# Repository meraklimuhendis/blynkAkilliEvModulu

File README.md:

# blynkAkilliEvModulu

Bu projede ESP8266-07 ile uzaktan akıllı ev kontrolü yaptım. Ayrıntılı olarak video halinde izlemek isterseniz aşağıdaki videoya gidebilirsiniz.

Video ► https://youtu.be/qkML5l_z_RQ

/*

MERAKLI MÜHENDİS YOUTUBE KANALI

Youtube Kanalı için - https://bit.ly/2AEP5bf

Facebook Sayfası için - https://bit.ly/3qVqAMC

Discord Kanalımıza GEL! - https://bit.ly/347FlSp

Tüm sorularınızı discord kanalımızdan sorabilirsiniz. Orası teknik servis gibi :)

*/

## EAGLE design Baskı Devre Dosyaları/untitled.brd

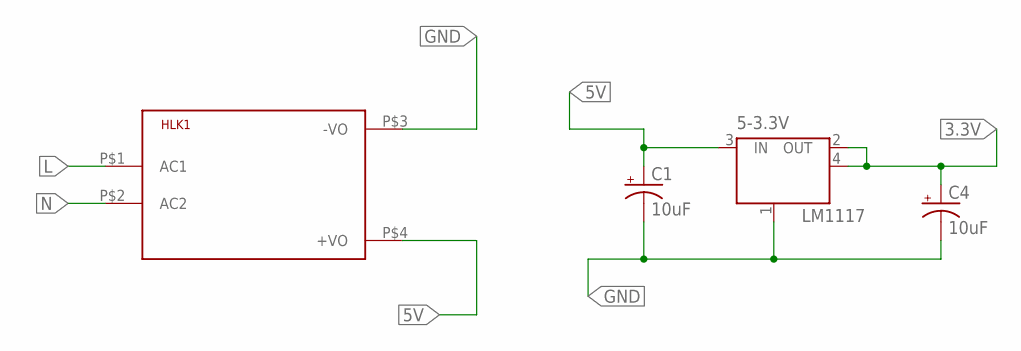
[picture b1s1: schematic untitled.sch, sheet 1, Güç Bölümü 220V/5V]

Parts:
5-3.3V: LM1117; SOT223
C1, C4: 10uF; EIA3216
HLK1: HLK-PM013W; HLK-PM01

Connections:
3.3V: 5-3.3V.2 (OUT), 5-3.3V.4 (OUT), C4.A (+); also elsewhere on the board
5V: 5-3.3V.3 (IN), C1.A (+), HLK1.P$4 (+VO); also elsewhere on the board
GND: 5-3.3V.1 (GND/ADJ), C1.C (-), C4.C (-), HLK1.P$3 (-VO); also elsewhere on the board
L: HLK1.P$1 (AC1); also elsewhere on the board
N: HLK1.P$2 (AC2); also elsewhere on the board

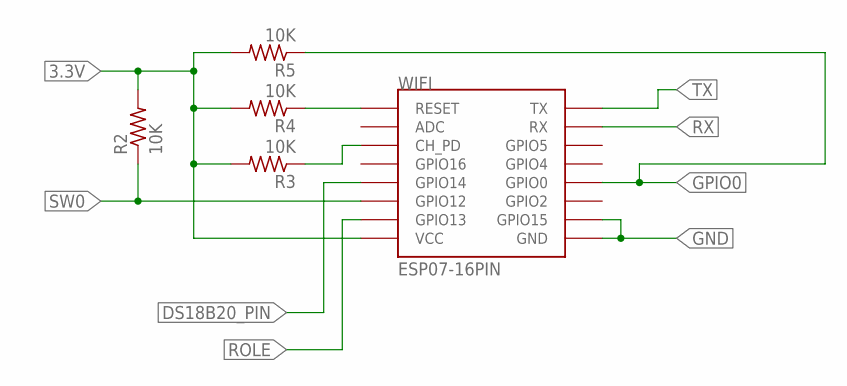
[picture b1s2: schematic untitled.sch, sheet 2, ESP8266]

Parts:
R2, R3, R4, R5: 10K; R0805
WIFI: ESP07-16PIN

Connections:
3.3V: R2.2, R3.2, R4.2, R5.2, WIFI.VCC; also elsewhere on the board
DS18B20_PIN: WIFI.GPIO14; also elsewhere on the board
GND: WIFI.GND, WIFI.GPIO15; also elsewhere on the board
GPIO0: R5.1, WIFI.GPIO0; also elsewhere on the board
unnamed: R4.1, WIFI.REST (RESET)
unnamed: R3.1, WIFI.CH_PD
ROLE: WIFI.GPIO13; also elsewhere on the board
RX: WIFI.RX; also elsewhere on the board
SW0: R2.1, WIFI.GPIO12; also elsewhere on the board
TX: WIFI.TX; also elsewhere on the board

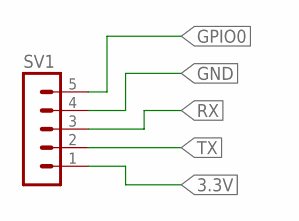
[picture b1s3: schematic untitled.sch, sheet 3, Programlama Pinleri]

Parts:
SV1: MA05-1

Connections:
3.3V: SV1.1; also elsewhere on the board
GND: SV1.4; also elsewhere on the board
GPIO0: SV1.5; also elsewhere on the board
RX: SV1.3; also elsewhere on the board
TX: SV1.2; also elsewhere on the board

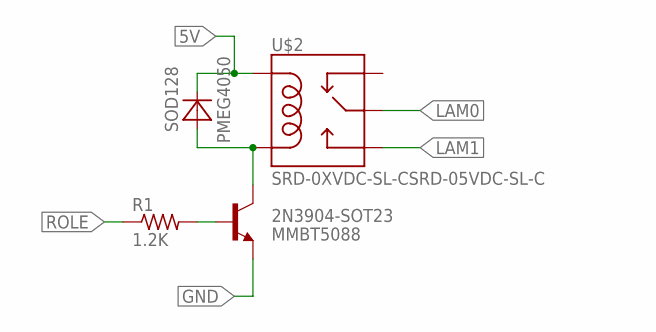
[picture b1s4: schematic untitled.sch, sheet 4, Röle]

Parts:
2N3904-SOT23: MMBT5088; SOT23-3
R1: 1.2K; R0805
SOD128: PMEG4050; SOD128
U$2: SRD-0XVDC-SL-CSRD-05VDC-SL-C; SRD-0XVDC-SL-C

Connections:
5V: SOD128.1 (C), U$2.COIL1; also elsewhere on the board
GND: 2N3904-SOT23.2 (E); also elsewhere on the board
LAM0: U$2.SWCOMMON; also elsewhere on the board
LAM1: U$2.SWOPEN; also elsewhere on the board
unnamed: 2N3904-SOT23.1 (B), R1.2
unnamed: 2N3904-SOT23.3 (C), SOD128.2 (A), U$2.COIL0
ROLE: R1.1; also elsewhere on the board

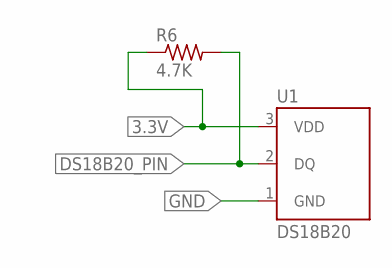
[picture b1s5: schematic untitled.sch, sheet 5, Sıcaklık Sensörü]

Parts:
R6: 4.7K; R0805
U1: DS18B20; TO-92-AMMO

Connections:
3.3V: R6.1, U1.3 (VDD); also elsewhere on the board
DS18B20_PIN: R6.2, U1.2 (DQ); also elsewhere on the board
GND: U1.1 (GND); also elsewhere on the board

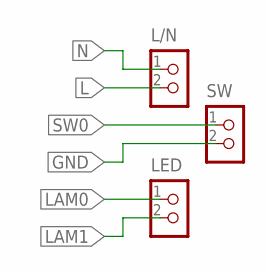
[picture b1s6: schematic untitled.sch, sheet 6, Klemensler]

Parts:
L/N: CON_TERMINAL_BLOCK_02-5MM; TERMINAL_BLOCK_2P_5
LED: CON_TERMINAL_BLOCK_02-5MM; TERMINAL_BLOCK_2P_5
SW: CON_TERMINAL_BLOCK_02-5MM; TERMINAL_BLOCK_2P_5

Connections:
GND: SW.2; also elsewhere on the board
L: L/N.2; also elsewhere on the board
LAM0: LED.1; also elsewhere on the board
LAM1: LED.2; also elsewhere on the board
N: L/N.1; also elsewhere on the board
SW0: SW.1; also elsewhere on the board

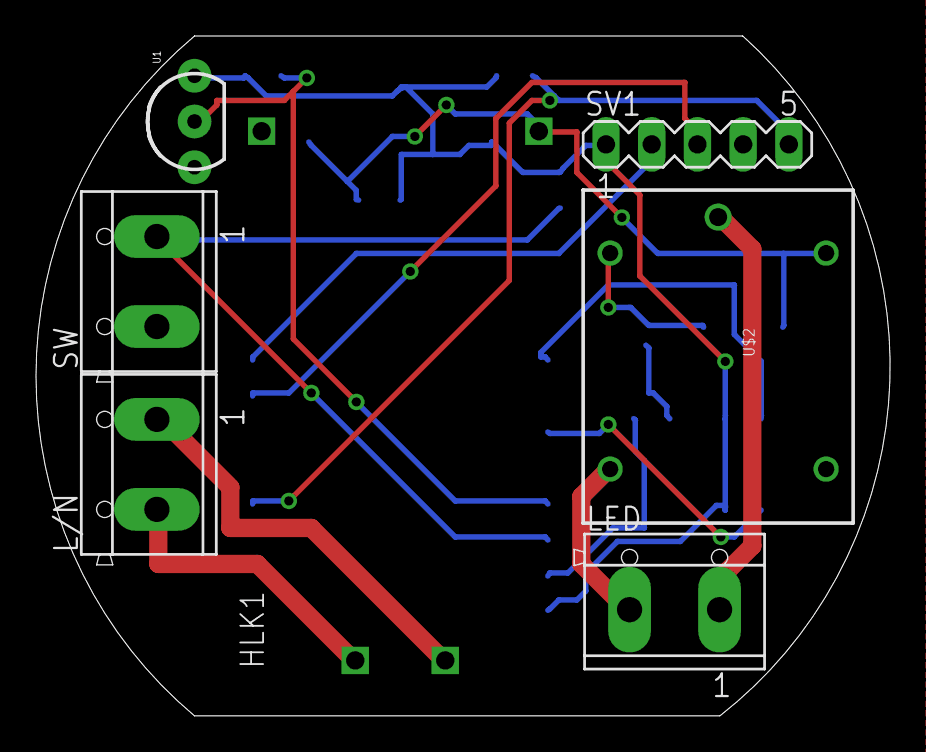
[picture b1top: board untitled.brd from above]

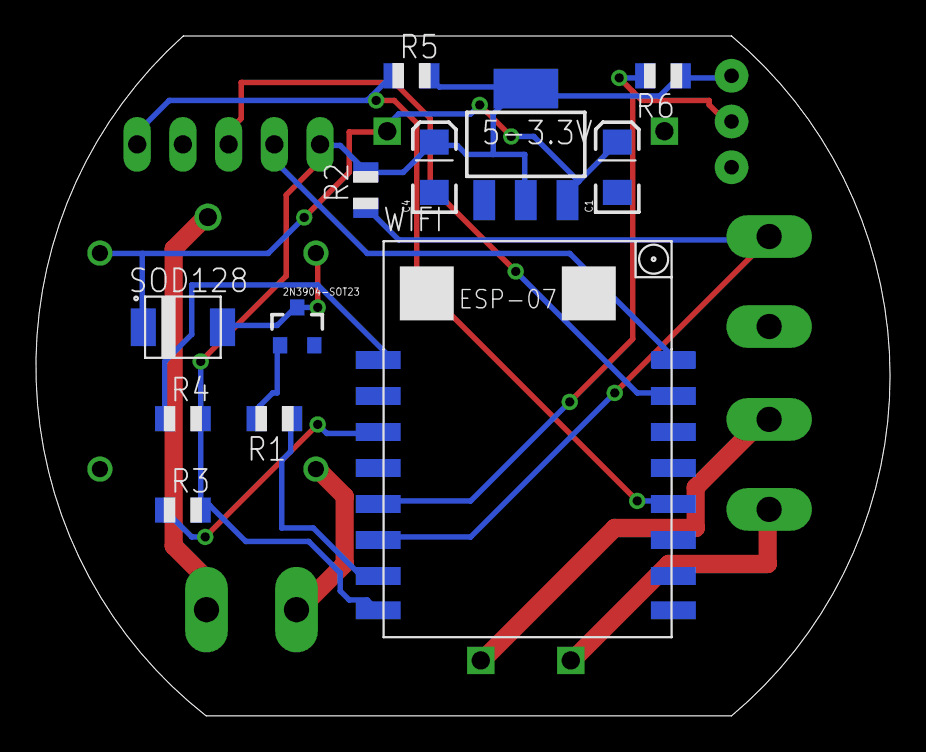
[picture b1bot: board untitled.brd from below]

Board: 2 copper layers, 47.4 x 37.8 mm, 19 parts (12 on the bottom side), 17 nets.

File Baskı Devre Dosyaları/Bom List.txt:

Partlist exported from C:/Users/Hp/Documents/eagle/AirCube/AirCube_V3/untitled.sch at 06/05/2019 11:09

Part         Value                        Device                       Package             Description                          PROD_ID     VALUE   
2N3904-SOT23 MMBT5088                     TRANSISTOR_NPNMMBT5088       SOT23-3             Generic NPN BJT                      TRANS-11160 MMBT5088
5-3.3V       LM1117                       LM1117                       SOT223                                                                       
C1           10uF                         10UF-TANT                    EIA3216             10uF Tantalum SMT                    CAP-00811   10uF    
C4           10uF                         10UF-TANT                    EIA3216             10uF Tantalum SMT                    CAP-00811   10uF    
HLK1         HLK-PM013W                   HLK-PM013W                   HLK-PM01            Hi-Link Power Supply                                     
L/N          CON_TERMINAL_BLOCK_02-5MM    CON_TERMINAL_BLOCK_02-5MM    TERMINAL_BLOCK_2P_5 2 poles wire to board terminal block                     
LAMBA        CON_TERMINAL_BLOCK_02-5MM    CON_TERMINAL_BLOCK_02-5MM    TERMINAL_BLOCK_2P_5 2 poles wire to board terminal block                     
PROG                                      MA05-1                       MA05-1              PIN HEADER                                               
R1           1.2K 0805                    R-US_R0805                   R0805               RESISTOR, American symbol                                
R2           10K 805 0.25W                R-US_R0805                   R0805               RESISTOR, American symbol                                
SOD128       PMEG4050                     PMEG4050                     SOD128              NXP PMEG4050 Schottky diode                              
SW           CON_TERMINAL_BLOCK_02-5MM    CON_TERMINAL_BLOCK_02-5MM    TERMINAL_BLOCK_2P_5 2 poles wire to board terminal block                     
U$2          SRD-0XVDC-SL-CSRD-05VDC-SL-C SRD-0XVDC-SL-CSRD-05VDC-SL-C SRD-0XVDC-SL-C      SRD-05VDC-SL-C                                           
WIFI         ESP07                        ESP07                        ESP07               ESP8266 Wifi module 07 & 08

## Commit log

2020-12-13 Create kaynak_kod
2020-12-13 Blynk ile Akıllı Ev Modülü V3
    Videosu için - https://youtu.be/qkML5l_z_RQ

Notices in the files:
parts and their libraries:
SparkFun-Retired: Licensing:Creative Commons ShareAlike 4.0 International - https://creativecommons.org/licenses/by-sa/4.0
